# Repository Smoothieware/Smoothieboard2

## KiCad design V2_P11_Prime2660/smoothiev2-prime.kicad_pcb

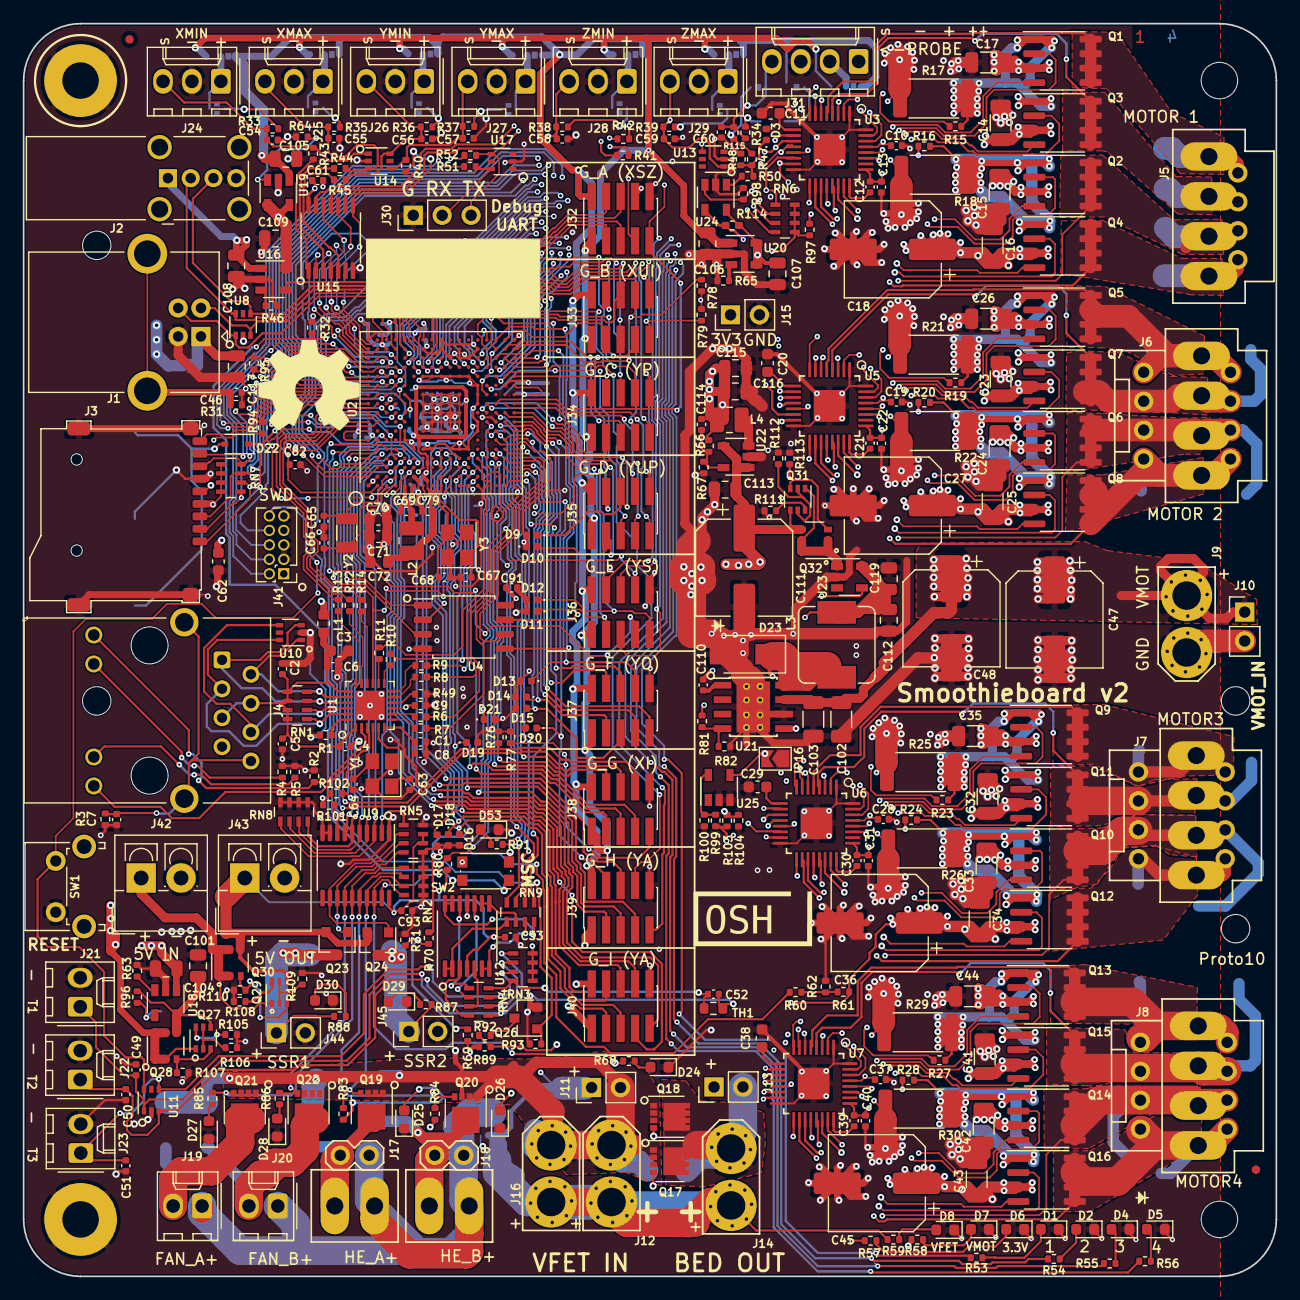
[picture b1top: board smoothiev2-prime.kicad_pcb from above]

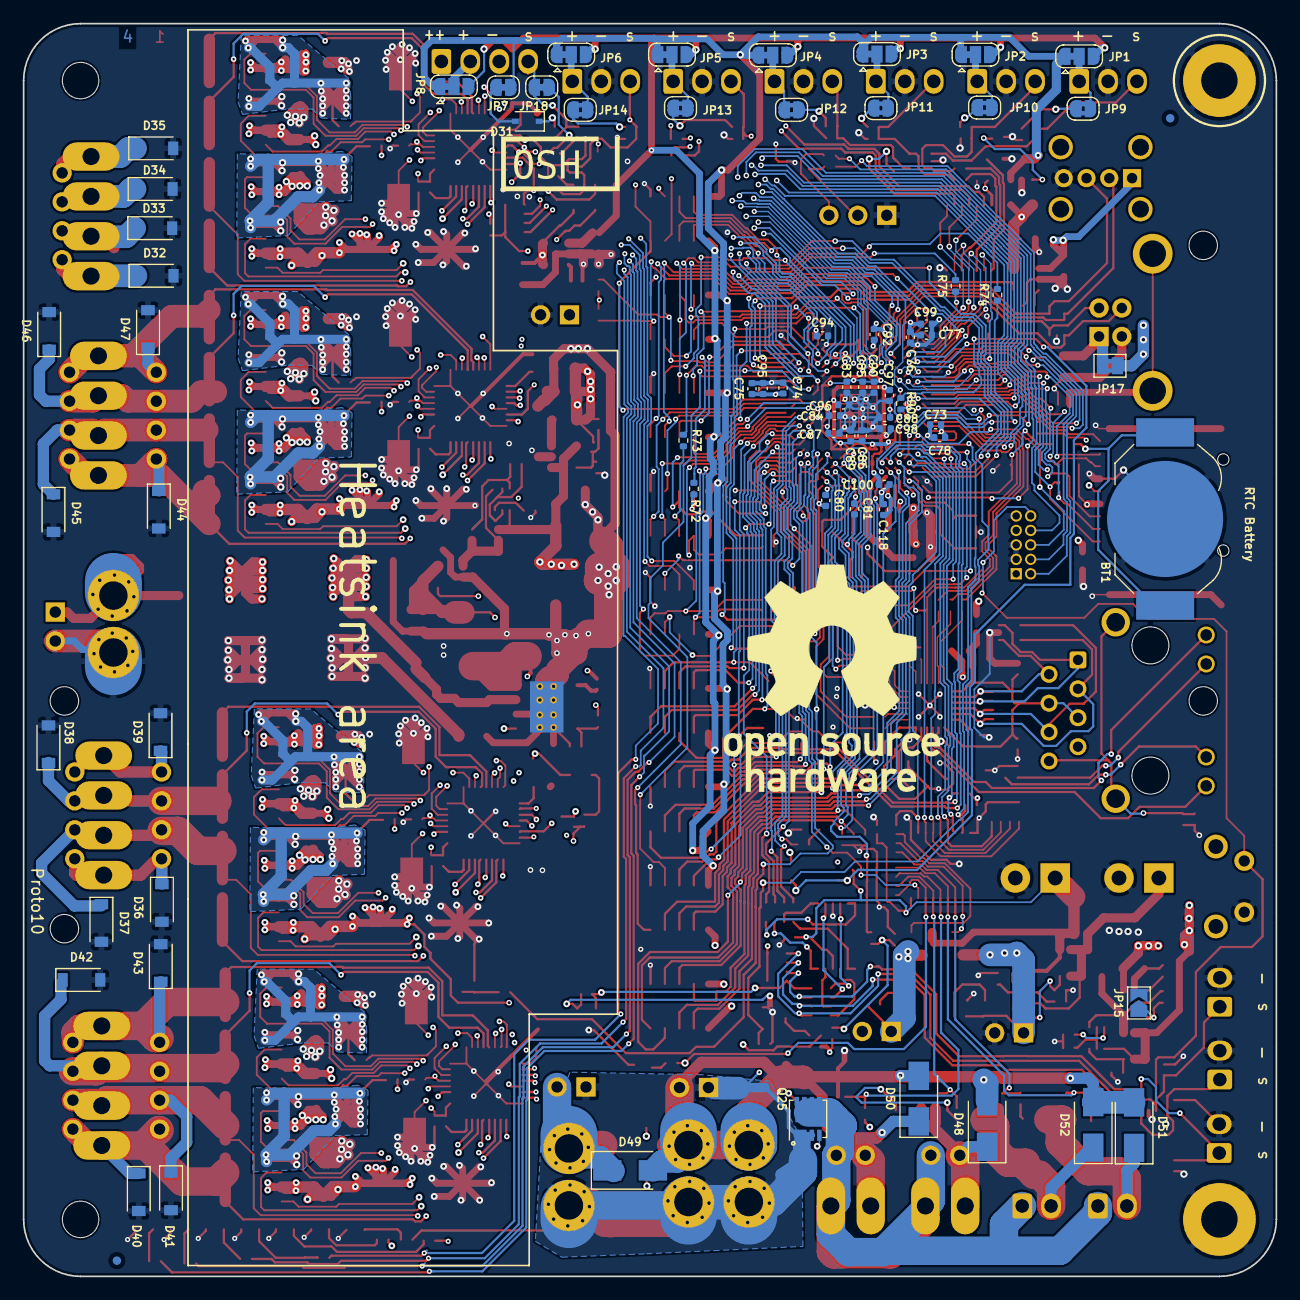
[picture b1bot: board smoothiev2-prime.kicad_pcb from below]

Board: 4 copper layers, 110.0 x 110.0 mm, 453 parts (75 on the bottom side), 377 nets.

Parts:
BT1: DNP; BatteryHolder_LINX_BAT-HLD-012-SMT
C1: 470p; C_0402_1005Metric
C2, C4, C5, C6, C9, C12, C21, C30, C39, C54, C55, C56, C57, C58, C59, C60, C81: 100n; C_0402_1005Metric
C3, C11, C20, C29, C38, C62, C70, C71, C72: 10u; C_0603_1608Metric
C7, C46: DNP; C_0402_1005Metric
C8, C10, C13, C19, C22, C28, C31, C37, C40, C49, C50, C51, C52, C53, C61, C73, C74, C75, C76, C77, C78, C79, C80, C82, C83, C84, C85, C86, C87, C88, C89, C90, C91, C92, C93, C94, C95, C96, C97, C98, C99, C100, C118: 1u; C_0402_1005Metric
C14, C15, C16, C17, C23, C24, C25, C26, C32, C33, C34, C35, C41, C42, C43, C44, C102, C103: 10u; C_1206_3216Metric
C18, C27, C36, C45, C47, C48, C111: CP; CP_Elec_8x11.9
C63, C64, C65, C66, C67, C68: 5.6p; C_0402_1005Metric
C69: 220p; C_0402_1005Metric
C101, C104, C105, C106, C107, C108, C109, C112, C113, C115, C116, C117, C119: 22u; C_0805_2012Metric
C110: 10n; C_0402_1005Metric
C114: 22p; C_0402_1005Metric
D1, D2, D4, D5, D6, D7, D8, D24, D25, D26, D27, D28, D29, D30, D53: LED; LED_0603_1608Metric
D3, D9, D10, D11, D12, D13, D14, D15, D16, D17, D18, D19, D20, D21: LESD8D3.3CAT5G; D_0402_1005Metric
D22: B5817WS; D_SOD-323
D23, D48, D49, D50, D51, D52: B340A; D_SMA
D31: D; D_SOD-323
D32, D33, D34, D35, D36, D37, D38, D39, D40, D41, D42, D43, D44, D45, D46, D47: SJD12C30L01; D_SOD-123
FID1, FID2, FID3, FID4: Fiducial; Fiducial_0.75mm_Dia_1.5mm_Outer
H1, H2: MountingHole; MountingHole_3.2mm_M3
H3, H4: MountingHole_Pad; MountingHole_3.2mm_M3_Pad
H5, H6, H7, H8: MountingHole; Stencil8_2.5mm
J1: USB_B; USB_B_OST_USB-B1HSxx_Horizontal
J2: USB_A; USB_A_Wuerth_614004134726_Horizontal
J3: Micro_SD_Card_Det; TF-01A
J4: RJ45_Hanrun_HR911105A
J5: Screw_Terminal_01x04; CONN_MOTOR
J6, J7, J8: Screw_Terminal_01x04; CONN_MOTOR2
J9, J12, J14, J16: Conn_01x02; XT30
J10, J11, J13, J15, J44, J45: Conn_01x02; PinHeader_1x02_P2.54mm_Vertical
J17, J18: Conn_01x02; CONN_SFET
J19, J20, J21, J22, J23: Conn_01x02; Molex_KK-254_AE-6410-02A_1x02_P2.54mm_Vertical
J24, J25, J26, J27, J28, J29: Conn_01x03; Molex_KK-254_AE-6410-03A_1x03_P2.54mm_Vertical
J30: Conn_01x03_Male; PinHeader_1x03_P2.54mm_Vertical
J31: Conn_01x04; Molex_KK-254_AE-6410-04A_1x04_P2.54mm_Vertical
J32, J33, J34, J35, J36, J37, J38, J39, J40: Conn_02x05_Odd_Even; PinHeader_2x05_P1.27mm_Vertical_SMD
J41: Conn_ARM_JTAG_SWD_10; PinHeader_2x05_P1.27mm_Vertical
J42, J43: Conn_01x02; TerminalBlock_4Ucon_1x02_P3.50mm_Vertical
JP1, JP2, JP3, JP4, JP5, JP6, JP8: SolderJumper_3_Bridged12; SolderJumper-3_P1.3mm_Bridged12_RoundedPad1.0x1.5mm
JP7: SolderJumper_2_Bridged; SolderJumper-2_P1.3mm_Bridged_RoundedPad1.0x1.5mm
JP9, JP10, JP11, JP12, JP13, JP14: SolderJumper_2_Bridged; SolderJumper-2_P1.3mm_Bridged2Bar_RoundedPad1.0x1.5mm
JP15, JP16: SolderJumper_2_Open; SolderJumper-2_P1.3mm_Open_TrianglePad1.0x1.5mm
JP17: SolderJumper_2_Bridged; SolderJumper-2_P1.3mm_Bridged2Bar_Pad1.0x1.5mm
JP18: Jumper_NC_Small; SolderJumper-2_P1.3mm_Bridged_RoundedPad1.0x1.5mm
L1: CBG160808U601T; L_0603_1608Metric
L2, L4: MHCD252012A-2R2M-A8S; L_1008_2520Metric
L3: YSPI0630A-220M; L_Sumida_CDMC6D28_7.25x6.5mm
LOGO1: Logo_Open_Hardware_Small; OSHW-Logo_19x20mm_SilkScreen
LOGO2: Logo_Open_Hardware_Small; OSHW-Symbol_8.9x8mm_SilkScreen
LOGO3, LOGO4: Logo_Open_Hardware_Small; OSHW_Dual_0.25_Scale
NT1, NT2, NT3, NT4, NT5, NT6, NT7, NT8: Net-Tie_2; NetTie-2_SMD_Pad2.0mm
NT9, NT11: Net-Tie_2; NetTie-2_SMD_Pad0.5mm
Q1, Q2, Q3, Q4, Q5, Q6, Q7, Q8, Q9, Q10, Q11, Q12, Q13, Q14, Q15, Q16: Si4542DY; SOIC-8_3.9x4.9mm_P1.27mm
Q17, Q18, Q19, Q20, Q21, Q22: WSD3066DN33; VSON-8_3.3x3.3mm_P0.65mm_NexFET
Q23, Q24: CJ2301 S1; SOT-23
Q25: WSD30L40DN; Vishay_PowerPAK_1212-8_Single
Q26: 2N7002; SOT-23
Q27, Q29, Q31: MBT3906DW1; SOT-363_SC-70-6
Q28, Q30, Q32: SQ3493EV; TSOP-6_1.65x3.05mm_P0.95mm
R1: 12.1k; R_0402_1005Metric
R2, R32, R33, R35, R36, R37, R38, R39, R49, R58, R59, R62, R71, R81, R90, R92, R93, R94, R95, R96, R101, R102, R105, R107, R108, R110, R111, R113: 10k; R_0402_1005Metric
R3, R31: DNP; R_0402_1005Metric
R4, R5, R34, R40, R41, R42, R43, R44, R45, R48, R50, R53, R54, R55, R56, R57, R60, R68, R70, R76, R77, R78, R79, R83, R84, R85, R86, R87, R88, R91, R98: 1k; R_0402_1005Metric
R6, R7, R8, R9, R10, R11, R12, R13, R14: 33R; R_0402_1005Metric
R15, R16, R19, R20, R23, R24, R27, R28: 47R; R_0402_1005Metric
R17, R18, R21, R22, R25, R26, R29, R30: R; R_2512_6332Metric
R46, R63, R67, R80: 4.7k; R_0402_1005Metric
R47, R104, R115: 7.1k; R_0402_1005Metric
R51, R52, R72, R73, R74, R75: 100R; R_0402_1005Metric
R61, R69, R106, R109, R112: 100k; R_0402_1005Metric
R64, R65, R66, R89, R100: 21.5k; R_0402_1005Metric
R82: 3.24k; R_0402_1005Metric
R97: 8.2k; R_0402_1005Metric
R99: 56k; R_0402_1005Metric
R103: 33k; R_0402_1005Metric
R114: 3.24k; R_0402_1005Metric_Pad0.72x0.64mm_HandSolder
RN1: 49.9R; R_Array_Concave_4x0603
RN2, RN5, RN6, RN7, RN8: 10k; R_Array_Concave_4x0603
RN3, RN4, RN9: 4.7k; R_Array_Concave_4x0603
SW1: SW_Push; SW_Tactile_SPST_Angled_PTS645Vx58-2LFS
SW2: TS-1185EC-C-D-B; SW_Push_1P1T_NO_CK_KMR2
TH1: R_0603_1608Metric
U1: LAN8720A; QFN-24-1EP_4x4mm_P0.5mm_EP2.6x2.6mm
U2: STM32H745XIHx; TFBGA-265_14x14mm_Layout17x17_P0.8mm
U3, U5, U6, U7: TMC2590; TMC2590-TA-T
U4: AT25SF081-SSHF-X; SOIC-8_5.23x5.23mm_P1.27mm
U8, U10, U11, U13, U14, U17: TPD4E1U06DCKR; SOT-363_SC-70-6
U9: 74HCT541; TSSOP-20_4.4x6.5mm_P0.65mm
U12: LMV324; TSSOP-14_4.4x5mm_P0.65mm
U15: 74LCX07; TSSOP-14_4.4x5mm_P0.65mm
U16, U18, U19, U20: MT9700; SOT-23-5
U21: TPS5430DDA; TI_SO-PowerPAD-8_ThermalVias
U22: MT3410L; SOT-23-5
U23: AP22814AW5; SOT-23-5
U24: LMV331; SOT-23-5
U25: BD4722G; SOT-23-5
Y1, Y3: Crystal_GND24; Crystal_SMD_3225-4Pin_3.2x2.5mm
Y2: Crystal; Crystal_SMD_3215-2Pin_3.2x1.5mm

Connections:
/1.2V_MCU: C72.1, C73.1, C74.1, C75.1, C76.1, C77.1, C78.1, C79.1, C95.1, C96.1, C97.1, C98.1, C99.1, C100.1, L2.1, U2.A6, U2.A7, U2.C17, U2.D17, U2.G2, U2.U11, U2.U12
/3V3: C9.1, C10.1, C19.1, C28.1, C37.1, C61.1, C62.1, C70.1, C71.1, C80.1, C83.1, C84.1, C85.1, C86.1, C87.1, C88.1, C89.1, C90.1, C91.1, C92.1, C94.1, C107.1, C114.2, C115.1, C116.1, C118.1, J3.4, J15.1, J41.1, L1.2, L4.1, R57.1, R66.1, R76.2, R77.2, R78.2, R79.2, R94.2, R95.2, R97.2, R101.2, R102.2, R114.1, RN3.5, RN3.6, RN3.7, RN3.8, RN6.5, RN6.6, RN6.7, RN6.8, RN7.1, RN7.2, RN7.3, RN7.4, SW2.2, U1.9, U2.E6, U2.E7, U2.E9, U2.E11, U2.F1, U2.F5, U2.F17, U2.G5, U2.G13, U2.G17, U2.H5, U2.H13, U2.J13, U2.K5, U2.K13, U2.L1, U2.L5, U2.L13, U2.M1, U2.M5, U2.M13, U2.N7, U2.N8, U2.N10, U2.N11, U2.N12, U2.P17, U3.29, U4.8, U5.29, U6.29, U7.29, U15.14, U20.4, U20.5, U24.5
/3V3_LIMIT: C106.1, J32.1, J33.1, J34.1, J35.1, J36.1, J37.1, J38.1, J39.1, J40.1, JP1.3, JP2.3, JP3.3, JP4.3, JP5.3, JP6.3, JP8.3, U20.1
/5V: C53.1, C93.1, C104.1, C109.1, C111.1, C113.1, J43.1, Q23.2, Q24.2, Q29.4, Q30.4, Q31.4, Q32.4, R80.2, RN5.2, RN5.3, U9.20, U12.4, U16.5, U18.1, U19.4, U19.5, U22.1, U22.4
/5V_IN: JP17.2, Q27.1, Q28.1, Q28.2, Q28.5, Q28.6
/5V_LIMIT: C105.1, J32.2, J33.2, J34.2, J35.2, J36.2, J37.2, J38.2, J39.2, J40.2, JP1.1, JP2.1, JP3.1, JP4.1, JP5.1, JP6.1, JP7.1, JP8.1, U19.1
/5V_PORTIN: J42.1, Q29.1, Q30.1, Q30.2, Q30.5, Q30.6
/ADC1_CH12: D19.1, J39.5, U2.M3
/ADC1_CH13: D21.1, J39.3, U2.M4
/ADC1_CH15: D20.1, J39.4, U2.U2
/ADC3_CH6: D16.1, J40.3, U2.L3
/ADC3_CH8: D17.1, J40.4, U2.K2
/ADC3_CH9: D18.1, J40.5, U2.J5
/BED_FET: RN5.5, U2.D3, U9.2
/BOOT0: R32.2, R90.2, SW2.1, U2.E8
/CARD_DET: J3.9, R94.1, U2.A9
/CS_A: RN6.1, U2.E10, U3.14
/CS_B: RN6.4, U2.F15, U5.14
/CS_C: RN6.3, U2.F16, U6.14
/CS_D: RN6.2, U2.G15, U7.14
/DIR_A: U2.A12, U3.30
/DIR_B: U2.H16, U5.30
/DIR_C: U2.H14, U6.30
/DIR_D: U2.G14, U7.30
/ESXMAX: U2.C14, U15.4
/ESXMIN: U2.D13, U15.2
/ESYMAX: U2.D15, U15.8
/ESYMIN: U2.A15, U15.6
/ESZMAX: U2.B16, U15.12
/ESZMIN: U2.A16, U15.10
/ETH_CRSDV: R8.2, U2.R5
/ETH_MDC: R10.2, U2.M2
/ETH_MDIO: R9.2, U2.N3
/ETH_RFCLK: R11.2, U2.N4
/ETH_RXD0: R6.2, U2.T4
/ETH_RXD1: R7.2, U2.U4
/ETH_TXD0: R12.2, U2.D9
/ETH_TXD1: R13.2, U2.C9
/ETH_TXEN: R14.2, U2.B9
/EXTRAFET: Q26.1, R93.2, U2.C11
/FANA_FET: RN8.7, U2.B4, U9.5
/FANB_FET: RN8.8, U2.F4, U9.6
/FETSENSE: R70.1, U2.K4
/HOTEND_A_FET: RN8.5, U2.C4, U9.3
/HOTEND_B_FET: RN8.6, U2.D5, U9.4
/I2C2_SCL: J38.9, R77.1, U2.G3
/I2C2_SDA: J38.8, R76.1, U2.G4
/I2C3_SCL: J33.9, R79.1, U2.E15
/I2C3_SDA: J33.8, R78.1, U2.T13
/ILED1: R53.1, U2.R13
/ILED2: R54.1, U2.P13
/ILED3: R55.1, U2.P14
/ILED4: R56.1, U2.R14
/MCU_DEBUG_RX: R51.1, U2.B11
/MCU_DEBUG_TX: R52.1, U2.A11
/MCU_RESET: C81.1, J41.10, SW1.2, U1.15, U2.K1, U11.6
/MOTSPI_CIPO: J32.8, U2.D1, U3.10, U5.10, U6.10, U7.10
/MOTSPI_COPI: J32.7, U2.E5, U3.11, U5.11, U6.11, U7.11
/MOTSPI_SCK: J32.9, U2.R10, U3.12, U5.12, U6.12, U7.12
/MOT_EN: U2.D16, U3.15, U5.15, U6.15, U7.15
/OUTPUTENABLE: R80.1, U2.P8, U9.19
/PA4: D15.1, J37.5, U2.U3
/PB1: D14.1, J37.3, U2.T5
/PB12: J39.9, U2.T14
/PC0: J38.5, U2.L2
/PC13: J40.9, U2.E3
/PD9: J33.3, U2.T17
/PD10: J34.5, U2.T16
/PD12: J34.4, U2.R16
/PD14: J34.3, U2.P16
/PD15: J36.6, U2.P15
/PE4: J40.7, U2.D2
/PE7: D10.2, J35.3, U2.U9
/PE8: D11.1, J36.3, U2.T9
/PF2: J39.6, U2.G1
/PF13: R91.1, U2.P7
/PF15: J38.6, U2.R9
/PG0: J37.6, U2.T8
/PG1: D13.1, J37.8, U2.U8
/PH2: J38.3, U2.N2
/PH3: J38.7, U2.P2
/PH4: J38.4, U2.P3
/PH7: J39.8, U2.U13
/PI8: J40.6, U2.E4
/PI9: J40.8, U2.E2
/PI10: J39.7, U2.F3
/PJ2: J37.9, U2.T6
/PJ3: J37.7, U2.U6
/PJ4: J37.4, U2.U7
/PJ6: J32.3, U2.N15
/PJ7: J36.4, U2.N14
/PJ8: J36.5, U2.N13
/PJ9: J32.4, U2.M14
/PJ10: J32.5, U2.L14
/PJ11: J32.6, U2.K14
/PK0: J33.6, U2.J14
/PK1: J33.7, U2.J15
/PROBE: R114.2, U2.P11, U24.4
/QSPI_CS: U2.B5, U4.1
/QSPI_IO0: U2.R15, U4.5
/QSPI_IO1: U2.L4, U4.2
/QSPI_IO2: U2.C3, U4.3
/QSPI_IO3: U2.R17, U4.7
/QSPI_SCK: U2.R6, U4.6
/SD_CK: J3.5, U2.C12
/SD_CMD: J3.3, RN7.7, U2.D12
/SD_D0: J3.7, RN7.8, U2.E13
/SD_D1: J3.8, R95.1, U2.E14
/SD_D2: J3.1, RN7.6, U2.A13
/SD_D3: J3.2, RN7.5, U2.B13
/SG_A: U2.B8, U3.27
/SG_B: U2.A8, U5.27
/SG_C: U2.B10, U6.27
/SG_D: U2.A10, U7.27
/SPI1_CIPO: J36.8, U2.R3
/SPI1_COPI: J36.7, U2.A5
/SPI1_SCK: D12.1, J36.9, U2.T3
/SSR1: R102.1, U2.A4, U9.7
/SSR2: R101.1, U2.C5, U9.8
/STEP_A: U2.B12, U3.31
/STEP_B: U2.H17, U5.31
/STEP_C: U2.H15, U6.31
/STEP_D: U2.F14, U7.31
/SWCLK: J41.4, U2.B14
/SWDIO: J41.2, U2.C15
/SWO: J41.6, U2.C6
/T1: RN9.1, U2.T1
/T2: RN9.2, U2.R7
/T3: RN9.3, U2.U5
/T4: RN9.4, U2.T7
/TDI: J41.8, U2.A14
/TIM1_CH1: D9.1, J35.6, U2.P9
/TIM1_CH2: J35.7, U2.P10
/TIM1_CH3: J35.8, U2.T10
/TIM1_CH4: J35.9, U2.U10
/TIM8_CH1: J34.6, U2.A3
/TIM8_CH2: J34.7, U2.A2
/TIM8_CH3: J34.8, U2.B3
/TIM8_CH4: J34.9, U2.B15
/USART3_RX: R73.1, U2.P12
/USART3_TX: R72.1, U2.U16
/USART4_RX: R75.1, U2.B17
/USART4_TX: R74.1, U2.D4
/USB_DEV_D+: J1.3, U2.E16, U8.1
/USB_DEV_D-: J1.2, U2.E17, U8.3
/USB_HOST_D+: J2.3, U2.T15, U8.4
/USB_HOST_D-: J2.2, U2.U15, U8.6
/USB_PWR: C108.1, J2.1, U16.1
/USB_PWR_ON: U2.U14, U16.4
/VBAT: C82.1, D22.1, U2.B1
/VMOT: C12.2, C13.1, C14.1, C15.1, C16.1, C17.1, C18.1, C21.2, C22.1, C23.1, C24.1, C25.1, C26.1, C27.1, C30.2, C31.1, C32.1, C33.1, C34.1, C35.1, C36.1, C39.2, C40.1, C41.1, C42.1, C43.1, C44.1, C45.1, C47.1, C48.1, C102.1, C103.1, J9.1, J10.1, J31.1, Q1.3, Q2.3, Q3.3, Q4.3, Q5.3, Q6.3, Q7.3, Q8.3, Q9.3, Q10.3, Q11.3, Q12.3, Q13.3, Q14.3, Q15.3, Q16.3, R58.1, R61.1, R99.2, R103.1, U3.25, U5.25, U6.25, U7.25, U21.7
/VMOTSENSE: R60.2, U2.P4
/XTAL_HSE_IN: C68.1, U2.J2, Y3.3
/XTAL_HSE_OUT: C67.1, U2.J1, Y3.1
/XTAL_LSE_IN: C65.1, U2.C2, Y2.1
/XTAL_LSE_OUT: C66.1, U2.C1, Y2.2
/driver-a/COIL_A1: D35.1, J5.4, Q1.5, Q1.6, Q1.7, Q1.8, U3.5
/driver-a/COIL_A2: D34.1, J5.3, Q3.5, Q3.6, Q3.7, Q3.8, U3.4
/driver-a/COIL_B1: D33.1, J5.2, Q2.5, Q2.6, Q2.7, Q2.8, U3.20
/driver-a/COIL_B2: D32.1, J5.1, Q4.5, Q4.6, Q4.7, Q4.8, U3.21
/driver-b/COIL_A1: D47.1, J6.4, Q5.5, Q5.6, Q5.7, Q5.8, U5.5
/driver-b/COIL_A2: D46.1, J6.3, Q7.5, Q7.6, Q7.7, Q7.8, U5.4
/driver-b/COIL_B1: D45.1, J6.2, Q6.5, Q6.6, Q6.7, Q6.8, U5.20
/driver-b/COIL_B2: D44.1, J6.1, Q8.5, Q8.6, Q8.7, Q8.8, U5.21
/driver-c/COIL_A1: D39.1, J7.4, Q9.5, Q9.6, Q9.7, Q9.8, U6.5
/driver-c/COIL_A2: D38.1, J7.3, Q11.5, Q11.6, Q11.7, Q11.8, U6.4
/driver-c/COIL_B1: D37.1, J7.2, Q10.5, Q10.6, Q10.7, Q10.8, U6.20
/driver-c/COIL_B2: D36.1, J7.1, Q12.5, Q12.6, Q12.7, Q12.8, U6.21
/driver-d/COIL_A1: D43.1, J8.4, Q13.5, Q13.6, Q13.7, Q13.8, U7.5
/driver-d/COIL_A2: D42.1, J8.3, Q15.5, Q15.6, Q15.7, Q15.8, U7.4
/driver-d/COIL_B1: D41.1, J8.2, Q14.5, Q14.6, Q14.7, Q14.8, U7.20
/driver-d/COIL_B2: D40.1, J8.1, Q16.5, Q16.6, Q16.7, Q16.8, U7.21
/ethernet/ETH_REFGND: C7.1, J4.8, J4.SH, R3.1
/ethernet/LED1: J4.12, U1.3
/ethernet/LED2: J4.9, R2.1, U1.2
/ethernet/TXD0: R12.1, U1.17
/ethernet/TXD1: R13.1, U1.18
/ethernet/TXEN: R14.1, U1.16
/expansion/GB_4: J33.4, R74.2
/expansion/GB_5: J33.5, R75.2
/expansion/GD_4: J35.4, R72.2
/expansion/GD_5: J35.5, R73.2
/mosfets/BED_GATE: Q17.4, Q18.4, R68.2, RN2.8, U9.18
/mosfets/CUTOFF_GATE: Q26.3, R92.1
/mosfets/FAN2_GATE: Q22.4, R86.2, RN5.8, U9.14
/mosfets/FAN_GATE: Q21.4, R85.2, RN2.5, U9.15
/mosfets/GND_FET: D48.2, D49.2, D50.2, D51.2, D52.2, J11.2, J12.2, J16.2, NT9.2, Q17.1, Q17.2, Q17.3, Q18.1, Q18.2, Q18.3, Q19.1, Q19.2, Q19.3, Q20.1, Q20.2, Q20.3, Q21.1, Q21.2, Q21.3, Q22.1, Q22.2, Q22.3
/mosfets/HEA_GATE: Q19.4, R83.2, RN2.7, U9.17
/mosfets/HEB_GATE: Q20.4, R84.2, RN2.6, U9.16
/mosfets/SSR1_G: Q23.1, RN5.7, U9.13
/mosfets/SSR2_G: Q24.1, RN5.6, U9.12
/mosfets/SW_BED: D49.1, J13.2, J14.2, Q17.5, Q18.5
/mosfets/VFET: J11.1, J12.1, J13.1, J14.1, J16.1, Q25.1, Q25.2, Q25.3, R59.1, R69.2, R89.2
/power/5v_REG: Q31.1, Q32.1, Q32.2, Q32.5, Q32.6, U23.1
/power/USB_IN: C101.1, Q27.4, Q28.4, R96.2, U18.5
/power/UVLO: JP16.2, R103.2, R104.1, U21.5, U23.4, U25.4
GND: BT1.2, C1.2, C2.2, C3.2, C4.2, C5.2, C6.2, C7.2, C8.2, C9.2, C10.2, C11.2, C12.1, C14.2, C15.2, C16.2, C17.2, C18.2, C19.2, C20.2, C21.1, C23.2, C24.2, C25.2, C26.2, C27.2, C28.2, C29.2, C30.1, C32.2, C33.2, C34.2, C35.2, C36.2, C37.2, C38.2, C39.1, C41.2, C42.2, C43.2, C44.2, C45.2, C46.2, C47.2, C48.2, C49.2, C50.2, C51.2, C53.2, C54.2, C55.2, C56.2, C57.2, C58.2, C59.2, C60.2, C61.2, C62.2, C63.2, C64.2, C65.2, C66.2, C67.2, C68.2, C69.2, C70.2, C71.2, C72.2, C73.2, C74.2, C75.2, C76.2, C77.2, C78.2, C79.2, C80.2, C81.2, C82.2, C83.2, C84.2, C85.2, C86.2, C87.2, C88.2, C89.2, C90.2, C91.2, C92.2, C93.2, C94.2, C95.2, C96.2, C97.2, C98.2, C99.2, C100.2, C101.2, C102.2, C103.2, C104.2, C105.2, C106.2, C107.2, C108.2, C109.2, C111.2, C112.2, C113.2, C115.2, C116.2, C117.2, C118.2, C119.2, D1.1, D2.1, D3.2, D4.1, D5.1, D6.1, D7.1, D8.1, D9.2, D10.1, D11.2, D12.2, D13.2, D14.2, D15.2, D16.2, D17.2, D18.2, D19.2, D20.2, D21.2, D23.2, D24.1, D25.1, D26.1, D27.1, D28.1, D29.1, D30.1, D32.2, D33.2, D34.2, D35.2, D36.2, D37.2, D38.2, D39.2, D40.2, D41.2, D42.2, D43.2, D44.2, D45.2, D46.2, D47.2, D53.1, H3.1, H4.1, J1.4, J2.4, J3.6, J3.10, J3.11, J9.2, J10.2, J15.2, J21.2, J22.2, J23.2, J24.2, J25.2, J26.2, J27.2, J28.2, J29.2, J30.1, J31.3, J32.10, J33.10, J34.10, J35.10, J36.10, J37.10, J38.10, J39.10, J40.10, J41.3, J41.5, J41.9, J42.2, J43.2, J44.2, J45.2, JP15.2, JP16.1, NT1.2, NT2.2, NT3.2, NT4.2, NT5.2, NT6.2, NT7.2, NT8.2, NT9.1, NT11.2, Q26.2, R1.2, R2.2, R3.2, R4.1, R5.1, R31.2, R32.1, R46.2, R48.1, R49.2, R62.2, R63.2, R64.2, R65.2, R67.2, R71.1, R82.2, R93.1, R98.1, R100.1, R104.2, R105.2, R106.2, R107.2, R108.2, R109.2, R110.2, R111.2, R112.2, R113.2, RN2.1, RN2.2, RN2.3, RN2.4, RN5.1, RN5.4, RN8.1, RN8.2, RN8.3, RN8.4, SW1.1, U1.25, U2.A1, U2.A17, U2.B2, U2.B6, U2.C10, U2.C13, U2.C16, U2.F2, U2.G7, U2.G8, U2.G9, U2.G10, U2.G11, U2.G16, U2.H7, U2.H8, U2.H9, U2.H10, U2.H11, U2.J3, U2.J7, U2.J8, U2.J9, U2.J10, U2.J11, U2.J16, U2.J17, U2.K7, U2.K8, U2.K9, U2.K10, U2.K11, U2.K15, U2.L7, U2.L8, U2.L9, U2.L10, U2.L11, U2.L15, U2.M15, U2.N1, U2.N16, U2.P1, U2.R4, U2.R8, U2.T12, U2.U1, U2.U17, U3.1, U3.16, U3.32, U3.33, U4.4, U5.1, U5.16, U5.32, U5.33, U6.1, U6.16, U6.32, U6.33, U7.1, U7.16, U7.32, U7.33, U8.2, U9.1, U9.9, U9.10, U10.2, U11.2, U12.11, U13.2, U14.2, U15.7, U16.2, U17.2, U18.2, U19.2, U20.2, U21.6, U21.9, U22.2, U23.2, U24.2, U25.2, U25.3, Y1.2, Y1.4, Y3.2, Y3.4
unnamed: BT1.1, D22.2
unnamed: C1.1, C8.1, U1.6
unnamed: C2.1, C3.1, C4.1, C5.1, C6.1, J4.4, J4.5, L1.1, RN1.5, RN1.6, RN1.7, RN1.8, U1.1, U1.19
unnamed: C11.1, U3.9
unnamed: C13.2, U3.24
unnamed: C20.1, U5.9
unnamed: C22.2, U5.24
unnamed: C29.1, U6.9
unnamed: C31.2, U6.24
unnamed: C38.1, U7.9
unnamed: C40.2, U7.24
unnamed: C46.1, J1.5, J2.5, R31.1
unnamed: C49.1, J21.1, RN3.1, RN4.1, U11.1
unnamed: C50.1, J22.1, RN3.2, RN4.2, U11.3
unnamed: C51.1, J23.1, RN3.3, RN4.3, U11.4
unnamed: C52.1, RN3.4, RN4.4, TH1.1
unnamed: C52.2, NT11.1, TH1.2
unnamed: C54.1, J24.3, R33.2, R43.2, U14.1
unnamed: C55.1, J25.3, R35.2, R44.2, U14.3
unnamed: C56.1, J26.3, R36.2, R45.2, U14.6
unnamed: C57.1, J27.3, R37.2, R40.2, U14.4
unnamed: C58.1, J28.3, R38.2, R41.2, U13.4
unnamed: C59.1, J29.3, R39.2, R42.2, U13.1
unnamed: C60.1, J31.4, JP18.1, R34.2, R115.2
unnamed: C63.1, U1.5, Y1.1
unnamed: C64.1, U1.4, Y1.3
unnamed: C69.1, L2.2, U2.E1
unnamed: C110.1, D23.1, L3.2, U21.8
unnamed: C110.2, U21.1
unnamed: C112.1, C119.1, L3.1, R81.1, U23.5
unnamed: C114.1, R66.2, R67.1, U22.5
unnamed: C117.1, J1.1, JP17.1
unnamed: D1.2, R53.2
unnamed: D2.2, R54.2
unnamed: D3.1, R47.1, R48.2, R50.2
unnamed: D4.2, R55.2
unnamed: D5.2, R56.2
unnamed: D6.2, R57.2
unnamed: D7.2, R58.2
unnamed: D8.2, R59.2
unnamed: D24.2, R68.1
unnamed: D25.2, R83.1
unnamed: D26.2, R84.1
unnamed: D27.2, R85.1
unnamed: D28.2, R86.1
unnamed: D29.2, R87.2
unnamed: D30.2, R88.2
unnamed: D31.1, R34.1
unnamed: D31.2, JP7.2
unnamed: D48.1, J17.2, Q19.5
unnamed: D50.1, J18.2, Q20.5
unnamed: D51.1, J19.2, Q21.5
unnamed: D52.1, J20.2, Q22.5
unnamed: D53.2, R91.2
unnamed: J4.1, RN1.3, U1.21, U10.3
unnamed: J4.2, RN1.4, U1.20, U10.1
unnamed: J4.3, RN1.1, U1.23, U10.6
unnamed: J4.6, RN1.2, U1.22, U10.4
unnamed: J4.10, R4.2
unnamed: J4.11, R5.2
unnamed: J17.1, J18.1, J19.1, J20.1, Q25.5
unnamed: J24.1, JP1.2, JP9.1
unnamed: J25.1, JP2.2, JP10.1
unnamed: J26.1, JP3.2, JP11.1
unnamed: J27.1, JP4.2, JP12.1
unnamed: J28.1, JP5.2, JP13.1
unnamed: J29.1, JP6.2, JP14.1
unnamed: J30.2, R51.2, U17.6
unnamed: J30.3, R52.2, U17.4
unnamed: J31.2, JP8.2
unnamed: J44.1, Q23.3, R88.1
unnamed: J45.1, Q24.3, R87.1
unnamed: JP9.2, R33.1
unnamed: JP10.2, R35.1
unnamed: JP11.2, R36.1
unnamed: JP12.2, R37.1
unnamed: JP13.2, R38.1
unnamed: JP14.2, R39.1
unnamed: JP15.1, R96.1, U18.4
unnamed: JP18.2, R47.2, R115.1
unnamed: L4.2, U22.3
unnamed: NT1.1, R17.2, U3.28
unnamed: NT2.1, R18.2, U3.13
unnamed: NT3.1, R21.2, U5.28
unnamed: NT4.1, R22.2, U5.13
unnamed: NT5.1, R25.2, U6.28
unnamed: NT6.1, R26.2, U6.13
unnamed: NT7.1, R29.2, U7.28
unnamed: NT8.1, R30.2, U7.13
unnamed: Q1.1, Q3.1, R15.1, R17.1
unnamed: Q1.2, U3.6
unnamed: Q1.4, U3.2
unnamed: Q2.1, Q4.1, R16.1, R18.1
unnamed: Q2.2, U3.19
unnamed: Q2.4, U3.23
unnamed: Q3.2, U3.7
unnamed: Q3.4, U3.3
unnamed: Q4.2, U3.18
unnamed: Q4.4, U3.22
unnamed: Q5.1, Q7.1, R19.1, R21.1
unnamed: Q5.2, U5.6
unnamed: Q5.4, U5.2
unnamed: Q6.1, Q8.1, R20.1, R22.1
unnamed: Q6.2, U5.19
unnamed: Q6.4, U5.23
unnamed: Q7.2, U5.7
unnamed: Q7.4, U5.3
unnamed: Q8.2, U5.18
unnamed: Q8.4, U5.22
unnamed: Q9.2, U6.6
unnamed: Q9.4, U6.2
unnamed: Q10.1, Q12.1, R24.1, R26.1
unnamed: Q10.2, U6.19
unnamed: Q10.4, U6.23
unnamed: Q9.1, Q11.1, R23.1, R25.1
unnamed: Q11.2, U6.7
unnamed: Q11.4, U6.3
unnamed: Q12.2, U6.18
unnamed: Q12.4, U6.22
unnamed: Q13.1, Q15.1, R27.1, R29.1
unnamed: Q13.2, U7.6
unnamed: Q13.4, U7.2
unnamed: Q14.1, Q16.1, R28.1, R30.1
unnamed: Q14.2, U7.19
unnamed: Q14.4, U7.23
unnamed: Q15.2, U7.7
unnamed: Q15.4, U7.3
unnamed: Q16.2, U7.18
unnamed: Q16.4, U7.22
unnamed: Q25.4, R89.1, R92.2
unnamed: Q27.2, Q27.5, R106.1
unnamed: Q27.3, Q28.3, R107.1
unnamed: Q27.6, R105.1
unnamed: Q29.2, Q29.5, R109.1
unnamed: Q29.3, Q30.3, R110.1
unnamed: Q29.6, R108.1
unnamed: Q31.2, Q31.5, R112.1
unnamed: Q31.3, Q32.3, R113.1
unnamed: Q31.6, R111.1
unnamed: R1.1, U1.24
unnamed: R6.1, U1.8
unnamed: R7.1, U1.7
unnamed: R8.1, U1.11
unnamed: R9.1, U1.12
unnamed: R10.1, U1.13
unnamed: R11.1, U1.14
unnamed: R15.2, U3.8
unnamed: R16.2, U3.17
unnamed: R19.2, U5.8
unnamed: R20.2, U5.17
unnamed: R23.2, U6.8
unnamed: R24.2, U6.17
unnamed: R27.2, U7.8
unnamed: R28.2, U7.17
unnamed: R40.1, U15.9
unnamed: R41.1, U15.11
unnamed: R42.1, U15.13
unnamed: R43.1, U15.1
unnamed: R44.1, U15.3
unnamed: R45.1, U15.5
unnamed: R46.1, U16.3
unnamed: R49.1, U1.10
unnamed: R50.1, U24.1
unnamed: R60.1, R61.2, R62.1
unnamed: R63.1, U18.3
unnamed: R64.1, U19.3
unnamed: R65.1, U20.3
unnamed: R69.1, R70.2, R71.2
unnamed: R81.2, R82.1, U21.4
unnamed: R90.1, U2.D10
unnamed: R97.1, R98.2, U24.3
unnamed: R99.1, R100.2, U25.5
unnamed: RN4.5, U12.12
unnamed: RN4.6, U12.10
unnamed: RN4.7, U12.5
unnamed: RN4.8, U12.3
unnamed: RN9.5, U12.1, U12.2
unnamed: RN9.6, U12.8, U12.9
unnamed: RN9.7, U12.6, U12.7
unnamed: RN9.8, U12.13, U12.14

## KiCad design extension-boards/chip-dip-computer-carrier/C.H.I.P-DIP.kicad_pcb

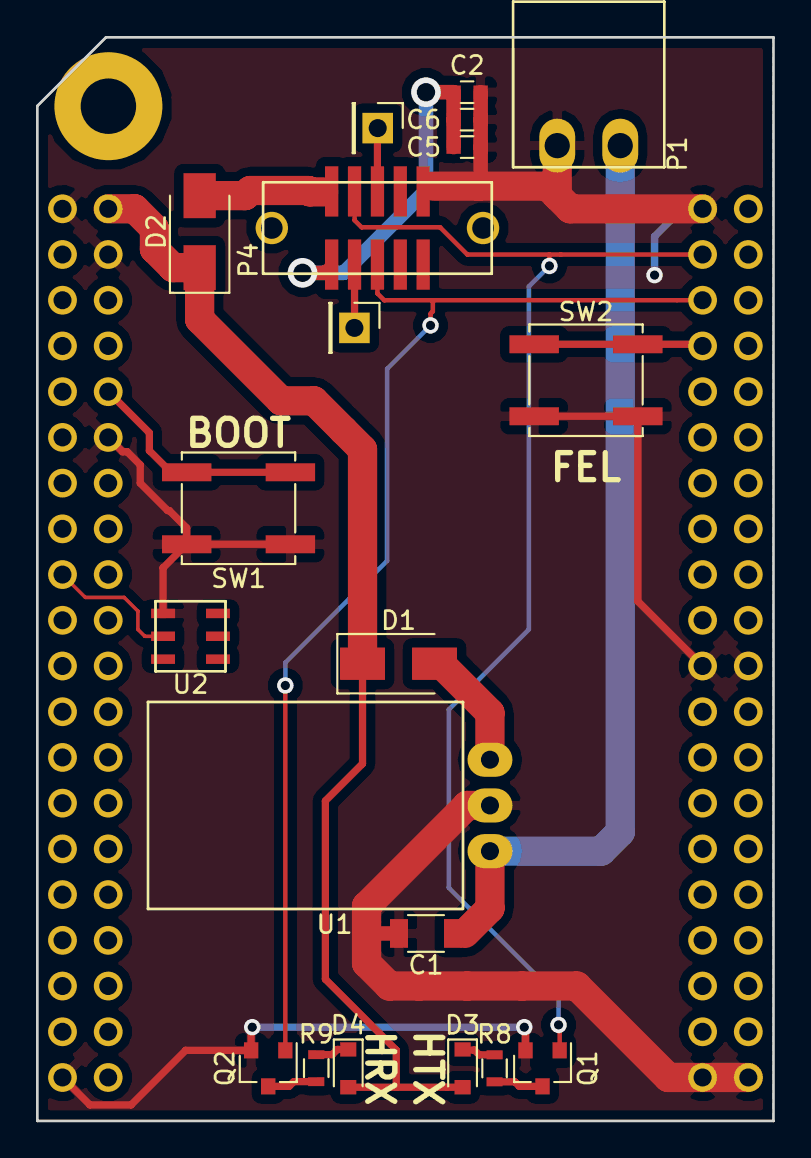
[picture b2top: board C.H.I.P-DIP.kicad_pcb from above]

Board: 2 copper layers, 40.9 x 60.2 mm, 21 parts (0 on the bottom side), 17 nets.

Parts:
C1: 3.3uF/100V; C_1206
C2: 10uF; C_0603
C5: 1uF; C_0603
C6: 0.1uF; C_0603
D1, D2: MBRA210LT3G; D_SMA_Standard
D3: HTX; D_0805
D4: HRX; D_0805
P1: CONN_01X02; FCI_20020110-C021A01LF
P2, P3: CONN_01X01; Pin_Header_Straight_1x01_Pitch2.54mm
P4: CONN_02X05; SHF-105-01-L-D-SM-LC
Q1, Q2: BSS214N; SOT-23
R8, R9: 220R; R_0603
SW1, SW2: SW_PUSH; SW_SPST_EVPBF
U1: R-78HB5.0-0.5L; R-78HBx.x-x.xL
U2: DS2431; TSOC-6
U3: C.H.I.P

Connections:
+3V3: C2.1, C5.1, C6.1, P4.1
+5V: D1.1, D2.1, D3.2, D4.2, U3.2
/HRXSTX: P4.5, Q2.1, U3.45
/HTXSRX: P4.4, Q1.1, U3.43
GND: C1.2, C2.2, C5.2, C6.2, P1.1, P4.10, Q1.2, Q2.2, SW1.1, SW2.1, U1.2, U2.1, U3.1, U3.4, U3.12, U3.39, U3.41, U3.61, U3.62, U3.79, U3.80
unnamed: C1.1, P1.2, U1.1
unnamed: D1.2, U1.3
unnamed: D2.2, P4.2
unnamed: D3.1, R8.2
unnamed: D4.1, R9.2
unnamed: P2.1, P4.3
unnamed: P3.1, P4.6
unnamed: Q1.3, R8.1
unnamed: Q2.3, R9.1
unnamed: SW1.2, U3.10
unnamed: SW2.2, U3.47
unnamed: U2.2, U3.17

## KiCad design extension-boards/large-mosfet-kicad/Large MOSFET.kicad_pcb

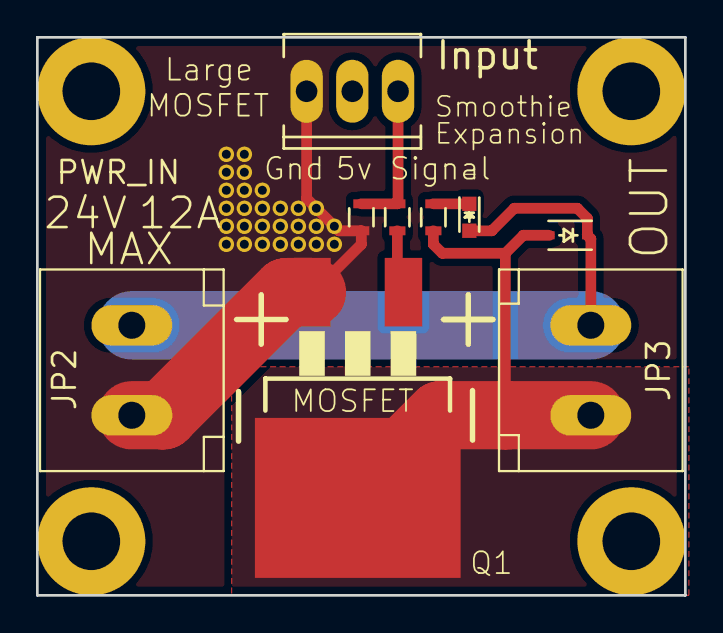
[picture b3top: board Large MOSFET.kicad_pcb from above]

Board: 2 copper layers, 36.0 x 31.0 mm, 40 parts (0 on the bottom side), 6 nets.

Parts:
D11: 1N4148; SOD-323
JP1: Input; Hdr_MOLEX-KK-RM2-54mm_Lock_3pin_straight
JP2: PWR_IN; Weidmuller_1715250000
JP3: OUT; Weidmuller_1715250000
LED7: LED; LED-0603
M1, M2, M3, M4: MH_3.2mm; M3_Mounting_Hole
Q1: MOSFET; D2PACK
R35: 10R; R_0603
R36: 100k; R_0603
R37: 1k5; R_0603
V1, V2, V3, V4, V5, V6, V7, V8, V9, V10, V11, V12, V13, V14, V15, V16, V17, V18, V19, V20, V21, V22, V23, V24, V25, V26, V27: VIA_GND; VIA_GND_0.86mm

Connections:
/E1-CONTROL: D11.2, JP3.1, Q1.2, R37.2
/FET-LOGIC-IN: JP1.3, R35.2, R36.2
/HEATERVIN: D11.1, JP2.1, JP3.2, LED7.2
GND: JP1.1, JP2.2, Q1.3, R36.1, V1.1, V2.1, V3.1, V4.1, V5.1, V6.1, V7.1, V8.1, V9.1, V10.1, V11.1, V12.1, V13.1, V14.1, V15.1, V16.1, V17.1, V18.1, V19.1, V20.1, V21.1, V22.1, V23.1, V24.1, V25.1, V26.1, V27.1
unnamed: LED7.1, R37.1
unnamed: Q1.1, R35.1

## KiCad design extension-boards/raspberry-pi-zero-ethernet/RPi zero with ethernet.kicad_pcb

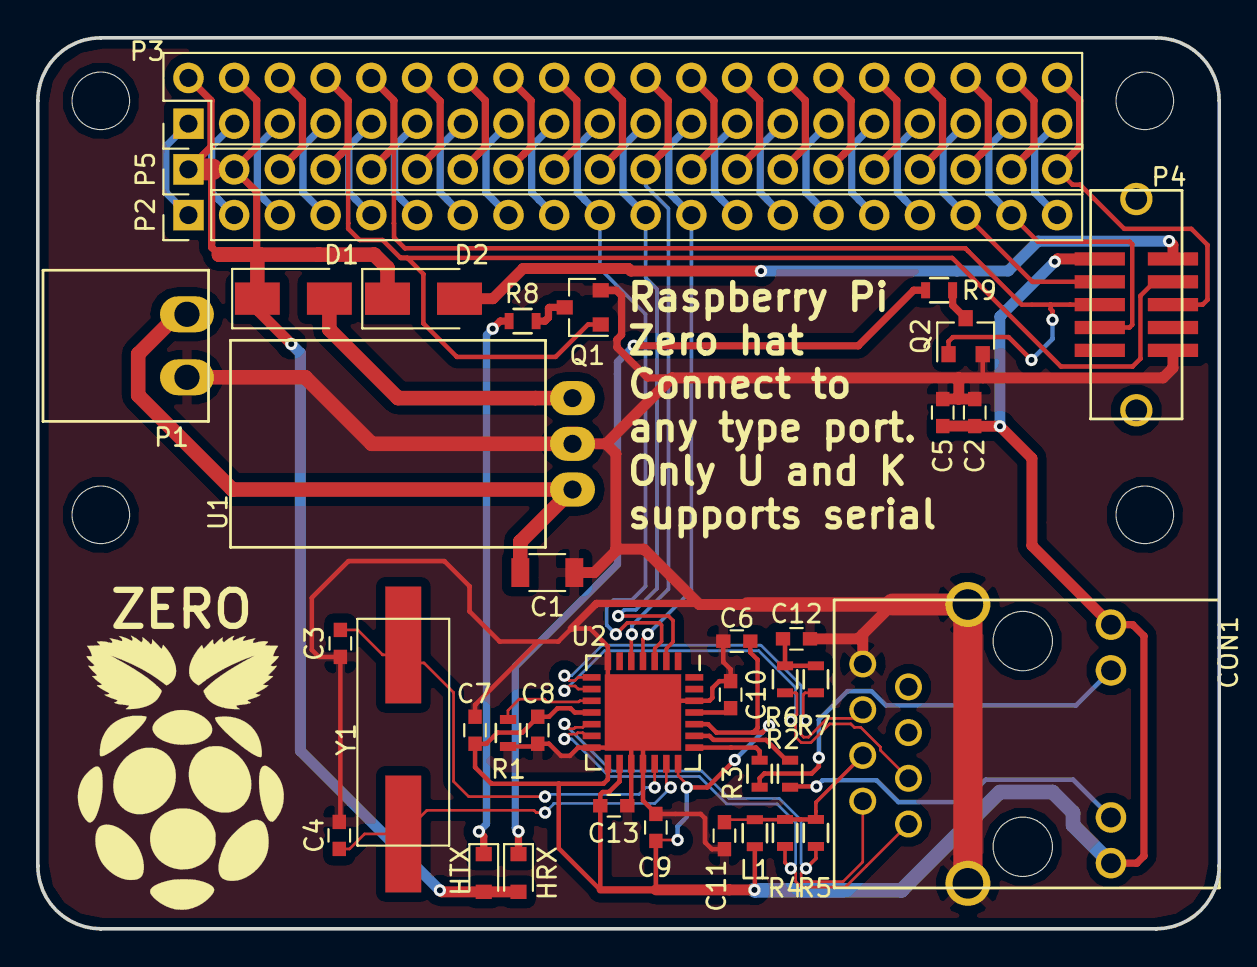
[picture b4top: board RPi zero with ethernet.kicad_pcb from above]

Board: 2 copper layers, 65.6 x 49.5 mm, 42 parts (0 on the bottom side), 54 nets.

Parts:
C1: 3.3uF/100V; C_1206
C2: 10uF; C_0603
C3, C4: 18pF; C_0603
C5: 1uF; C_0603
C6, C7, C8, C9, C11, C12, C13: 0.1uF; C_0603
C10: 10uF lowesr; C_0603
CON1: HR911105A
D1, D2: MBRA210LT3G; SMA_Standard
D3: HTX; D_0805
D4: HRX; D_0805
L1: MPZ1608S300A; R_0603
M1, M2, M3, M4: MH_M3; MountingHole_3.2mm_M3
P1: CONN_01X02; FCI_20020110-C021A01LF
P2, P5: CONN_01X20; Pin_Header_Straight_1x20_Pitch2.54mm
P3: CONN_02X20; Pin_Header_Straight_2x20_Pitch2.54mm
P4: CONN_02X05; SHF-105-01-L-D-SM-LC
Q1, Q2: BSS214N; SOT-23
R1: 2k32 1%; R_0603
R2, R3, R8, R9: 220R; R_0603
R4, R5, R6, R7: 49R9; R_0603
U1: R-78HB5.0-0.5L; R-78HBx.x-x.xL
U2: ENC28J60-I/ML; QFN-28-1EP_6x6mm_Pitch0.65mm
Y1: 25MHz; Crystal_SMD_HC49-SD

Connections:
+3V3: C2.1, C5.1, C6.1, C7.1, C8.1, C9.1, C13.1, CON1.9, CON1.12, L1.1, P4.1, U2.11, U2.15, U2.16, U2.21, U2.24
+5V: D1.1, D2.1, D3.2, D4.2, P3.2, P3.4, P5.1, P5.2
/3v3-pi: P2.1, P2.9, P3.1, P3.17
/CS: P3.22, P5.11, U2.5
/GPIO02: P2.2, P3.3
/GPIO03: P2.3, P3.5
/GPIO04: P2.4, P3.7
/GPIO05: P2.15, P3.29
/GPIO06: P2.16, P3.31
/GPIO07: P3.26, P5.13
/GPIO08: P3.24, P5.12
/GPIO012: P3.32, P5.16
/GPIO013: P2.17, P3.33
/GPIO016: P3.36, P5.18
/GPIO017: P2.6, P3.11
/GPIO018: P3.12, P5.6
/GPIO019: P2.18, P3.35, P4.3
/GPIO020: P3.38, P5.19
/GPIO021: P3.40, P4.6, P5.20
/GPIO022: P2.8, P3.15
/GPIO023: P3.16, P5.8
/GPIO024: P3.18, P5.9
/GPIO026: P2.19, P3.37, P4.7
/GPIO027: P2.7, P3.13
/Ground: P2.5, P2.13, P2.20, P3.6, P3.9, P3.14, P3.20, P3.25, P3.30, P3.34, P3.39, P5.3, P5.7, P5.10, P5.15, P5.17
/HRXSTX: P3.10, P4.5, P5.5, Q2.1
/HTXSRX: P3.8, P4.4, P5.4, Q1.1
/ID_SC: P3.28, P5.14
/ID_SD: P2.14, P3.27
/MISO: P2.11, P3.21, U2.2
/MOSI: P2.10, P3.19, U2.3
/RX_N: CON1.6, R7.1, U2.8
/RX_P: CON1.3, R6.2, U2.9
/SCK: P2.12, P3.23, U2.4
/TX_N: CON1.2, R5.1, U2.12
/TX_P: CON1.1, R4.2, U2.13
GND: C1.2, C2.2, C3.2, C4.2, C5.2, C6.2, C7.2, C8.2, C9.2, C10.2, C11.2, C12.2, C13.2, CON1.8, CON1.13, P1.1, P4.10, Q1.2, Q2.2, R1.2, U1.2, U2.7, U2.14, U2.17, U2.18, U2.26, U2.29
unnamed: C1.1, P1.2, U1.1
unnamed: C3.1, U2.19, Y1.1
unnamed: C4.1, U2.20, Y1.2
unnamed: C10.1, U2.25
unnamed: C11.1, CON1.4, L1.2, R4.1, R5.2
unnamed: C12.1, R6.1, R7.2
unnamed: CON1.10, R2.1
unnamed: CON1.11, R3.1
unnamed: D1.2, U1.3
unnamed: D2.2, P4.2
unnamed: D3.1, R8.2
unnamed: D4.1, R9.2
unnamed: Q1.3, R8.1
unnamed: Q2.3, R9.1
unnamed: R1.1, U2.10
unnamed: R2.2, U2.23
unnamed: R3.2, U2.22

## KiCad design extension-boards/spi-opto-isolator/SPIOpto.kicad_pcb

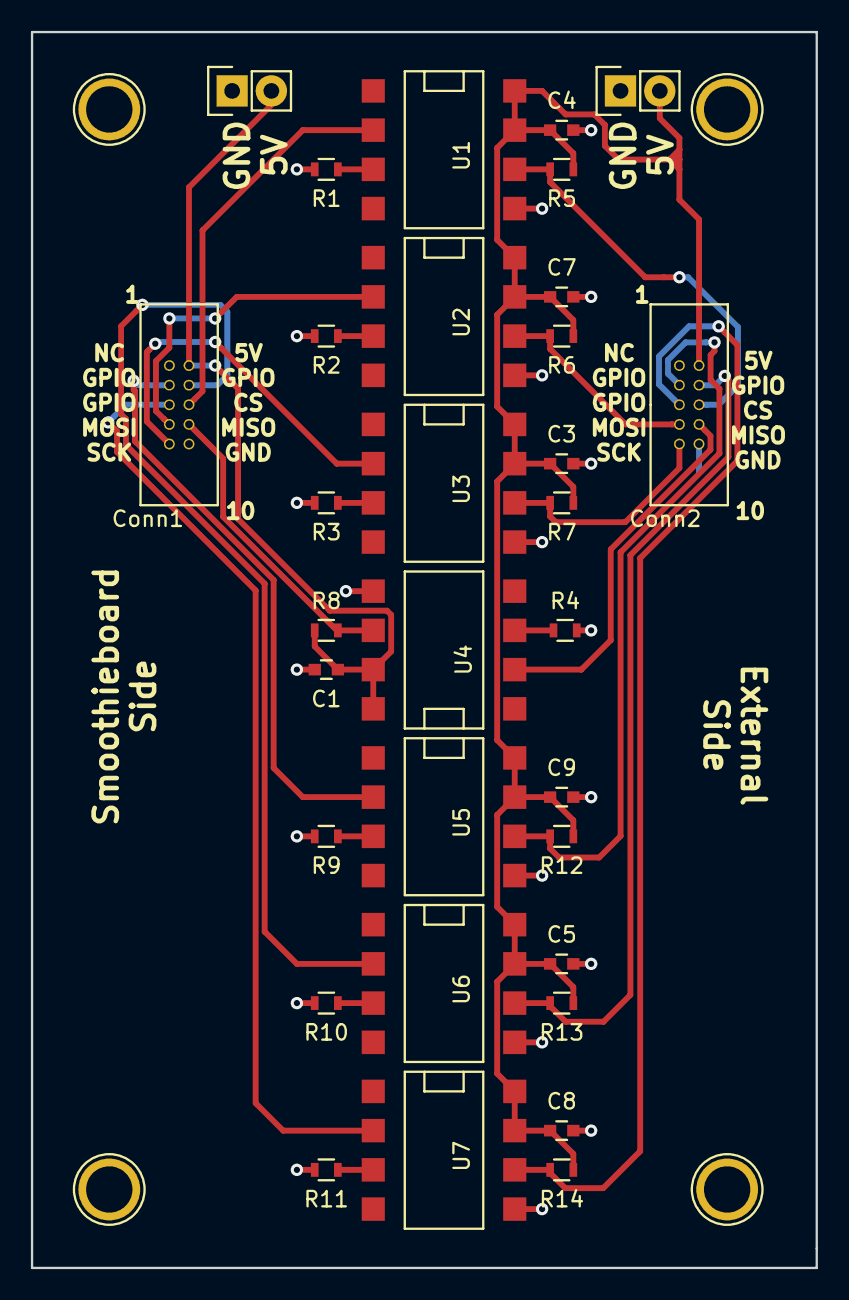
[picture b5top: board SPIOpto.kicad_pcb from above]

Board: 2 copper layers, 50.8 x 80.0 mm, 32 parts (0 on the bottom side), 25 nets.

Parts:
C1, C3, C4, C5, C7, C8, C9: u10; C_0603
Conn1, Conn2: Gadgeteer; SWDHeader
P1, P2: CONN_01X02; Pin_Header_Straight_1x02
R1, R2, R3, R4, R5, R6, R7, R8, R9, R10, R11, R12, R13, R14: 330R; R_0603
U1, U2, U3, U4, U5, U6, U7: 6N137S-TA1; OptoCouplerFootprint

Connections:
+5V: C1.1, Conn1.2, P1.2, R8.1, U4.7, U4.8
CS: Conn1.6, U1.2
CSOpto: Conn2.6, R5.2, U1.6
External5V: C3.1, C4.1, C5.1, C7.1, C8.1, C9.1, Conn2.2, P2.2, R5.1, R6.1, R7.1, R12.1, R13.1, R14.1, U1.7, U1.8, U2.7, U2.8, U3.7, U3.8, U5.7, U5.8, U6.7, U6.8, U7.7, U7.8
ExternalGND: C3.2, C4.2, C5.2, C7.2, C8.2, C9.2, Conn2.10, P2.1, R4.2, U1.5, U2.5, U3.5, U5.5, U6.5, U7.5
GND: C1.2, Conn1.10, P1.1, R1.2, R2.2, R3.2, R9.2, R10.2, R11.2, U4.5
GPIO0: Conn1.3, U5.2
GPIO1: Conn1.4, U6.2
GPIO1Opto: Conn2.4, R13.2, U6.6
GPIO2: Conn1.5, U7.2
GPIO2Opto: Conn2.5, R14.2, U7.6
GPIOOpto: Conn2.3, R12.2, U5.6
MISO: Conn1.8, R8.2, U4.6
MISOOpto: Conn2.8, U4.2
MOSI: Conn1.7, U2.2
MOSIOpto: Conn2.7, R6.2, U2.6
unnamed: R1.1, U1.3
unnamed: R2.1, U2.3
unnamed: R3.1, U3.3
unnamed: R4.1, U4.3
unnamed: R9.1, U5.3
unnamed: R10.1, U6.3
unnamed: R11.1, U7.3
SCK: Conn1.9, U3.2
SCKOpto: Conn2.9, R7.2, U3.6

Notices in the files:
parts and their libraries:
Copyright 2016 Accelerated Designs. All rights reserved.
